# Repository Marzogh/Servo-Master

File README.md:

# Servo-Master
A family of servo controllers based on AVR µCs

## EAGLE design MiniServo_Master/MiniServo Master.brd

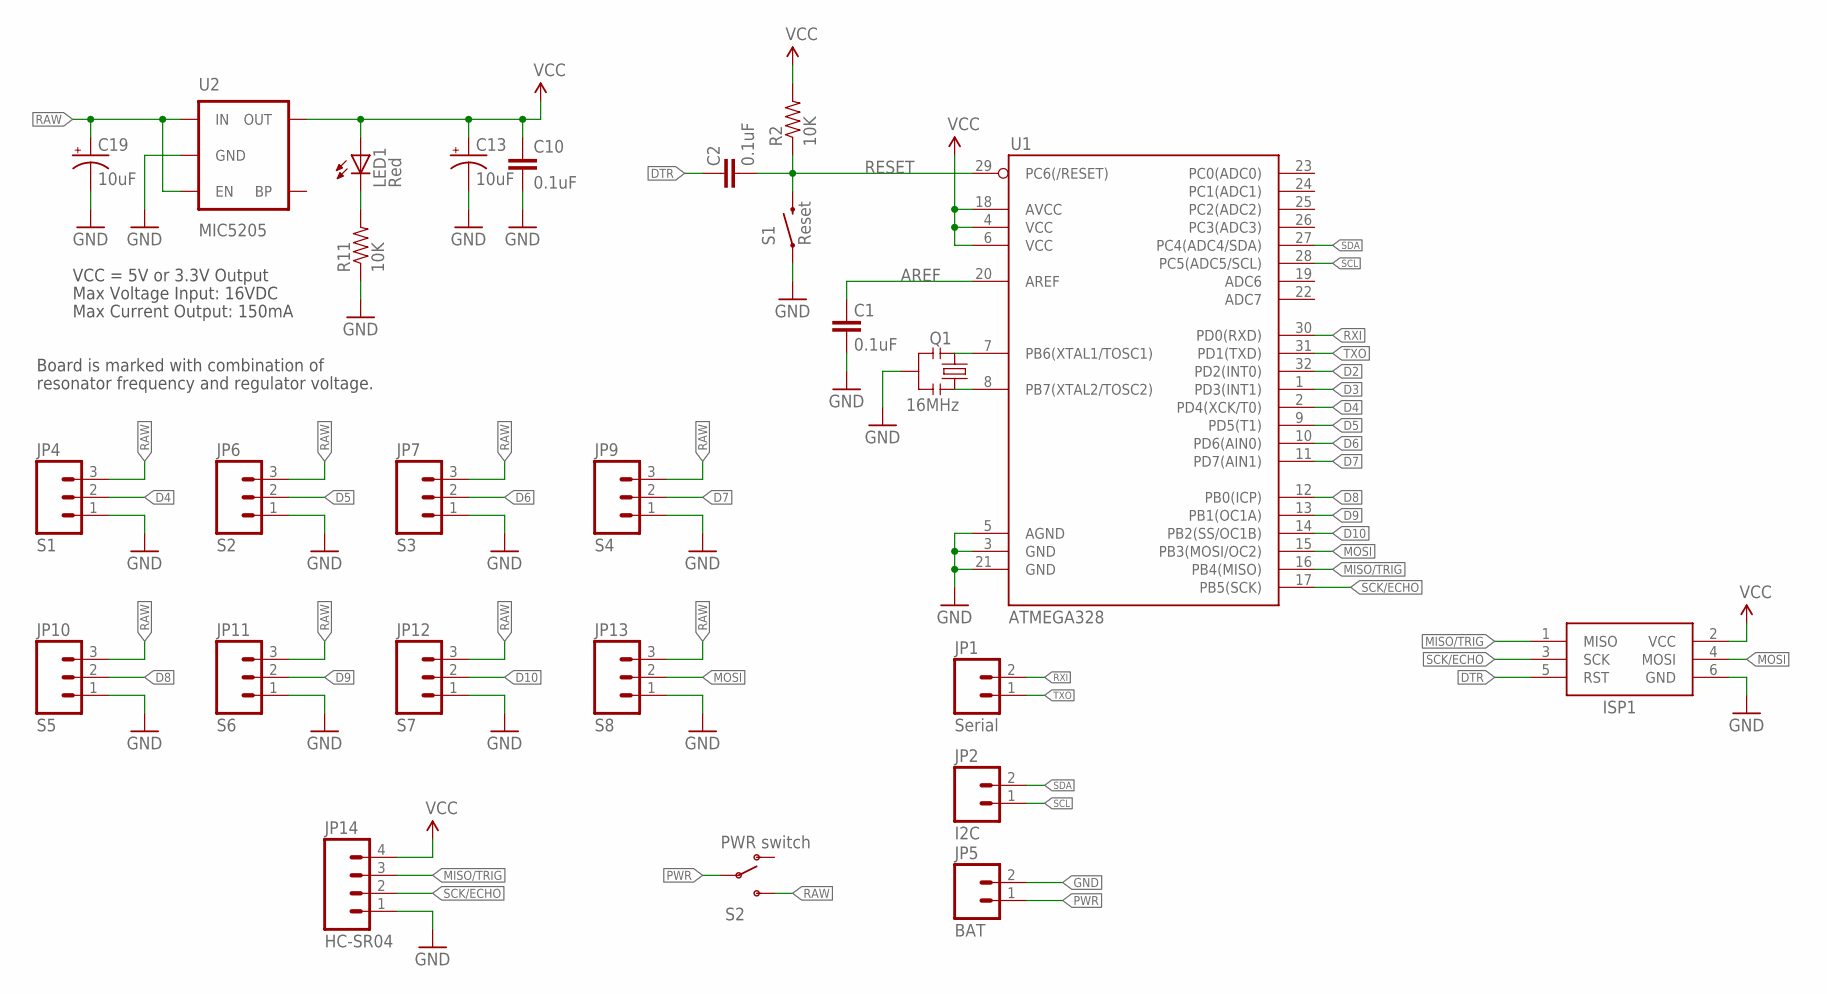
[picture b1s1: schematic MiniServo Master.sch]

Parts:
C1, C2, C10: 0.1uF; 0603-CAP
C13, C19: 10uF; EIA3216
ISP1: AVRISP-6; AVRISP
JP1: Serial; 1X02_NO_SILK
JP2: I2C; 1X02_NO_SILK
JP4: S1; 1X03_NO_SILK
JP5: BAT; 1X02_NO_SILK
JP6: S2; 1X03_NO_SILK
JP7: S3; 1X03_NO_SILK
JP9: S4; 1X03_NO_SILK
JP10: S5; 1X03_NO_SILK
JP11: S6; 1X03_NO_SILK
JP12: S7; 1X03_NO_SILK
JP13: S8; 1X03_NO_SILK
JP14: HC-SR04; 1X04_NO_SILK
LED1: Red; 0603-LED-ALT1
Q1: 16MHz; RESONATOR-SMD-1:1
R2, R11: 10K; 0603-RES
S1: Reset; TACTILE-SWITCH-SMD-ALT01
S2: PWR switch; SWITCH-SPST-SMD-A
U1: ATMEGA328; TQFP32-08
U2: MIC5205; SOT23-5

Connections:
3.3V: ISP1.2 (VCC), JP14.4
AREF: C1.2, U1.20 (AREF)
D2: U1.32 (PD2(INT0))
D3: U1.1 (PD3(INT1))
D4: JP4.2, U1.2 (PD4(XCK/T0))
D5: JP6.2, U1.9 (PD5(T1))
D6: JP7.2, U1.10 (PD6(AIN0))
D7: JP9.2, U1.11 (PD7(AIN1))
D8: JP10.2, U1.12 (PB0(ICP))
D9: JP11.2, U1.13 (PB1(OC1A))
D10: JP12.2, U1.14 (PB2(SS/OC1B))
DTR: C2.2, ISP1.5 (RST)
GND: C1.1, C10.2, C13.C (-), C19.C (-), ISP1.6 (GND), JP4.1, JP5.2, JP6.1, JP7.1, JP9.1, JP10.1, JP11.1, JP12.1, JP13.1, JP14.1, Q1.2, R11.1, S1.1, S1.2 (1), U1.3 (GND), U1.5 (AGND), U1.21 (GND), U2.2 (GND)
MISO/TRIG: ISP1.1 (MISO), JP14.3, U1.16 (PB4(MISO))
MOSI: ISP1.4 (MOSI), JP13.2, U1.15 (PB3(MOSI/OC2))
unnamed: Q1.3, U1.8 (PB7(XTAL2/TOSC2))
unnamed: Q1.1, U1.7 (PB6(XTAL1/TOSC1))
unnamed: LED1.C, R11.2
PWR: JP5.1, S2.2
RAW: C19.A (+), JP4.3, JP6.3, JP7.3, JP9.3, JP10.3, JP11.3, JP12.3, JP13.3, S2.3 (S), U2.1 (IN), U2.3 (EN)
RESET: C2.1, R2.1, S1.3 (2), S1.4 (2), U1.29 (PC6(/RESET))
RXI: JP1.2, U1.30 (PD0(RXD))
SCK/ECHO: ISP1.3 (SCK), JP14.2, U1.17 (PB5(SCK))
SCL: JP2.1, U1.28 (PC5(ADC5/SCL))
SDA: JP2.2, U1.27 (PC4(ADC4/SDA))
TXO: JP1.1, U1.31 (PD1(TXD))
VCC: C10.1, C13.A (+), LED1.A, R2.2, U1.4 (VCC), U1.6 (VCC), U1.18 (AVCC), U2.5 (OUT)

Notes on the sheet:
Max Voltage Input: 16VDC
Max Current Output: 150mA
Board is marked with combination of
resonator frequency and regulator voltage.
VCC = 5V or 3.3V Output

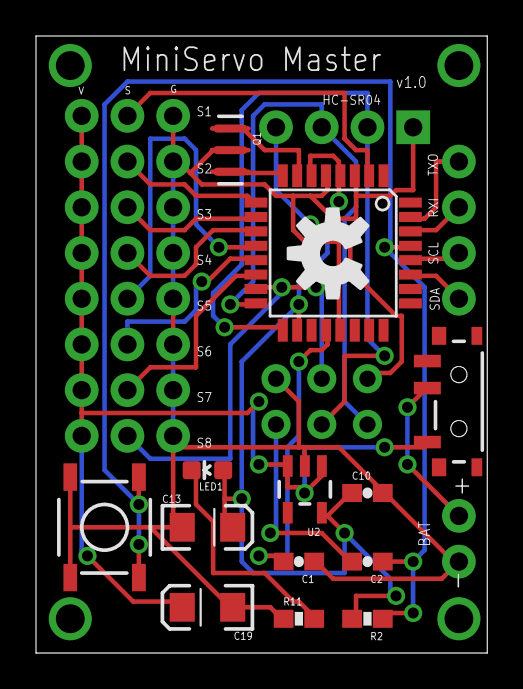
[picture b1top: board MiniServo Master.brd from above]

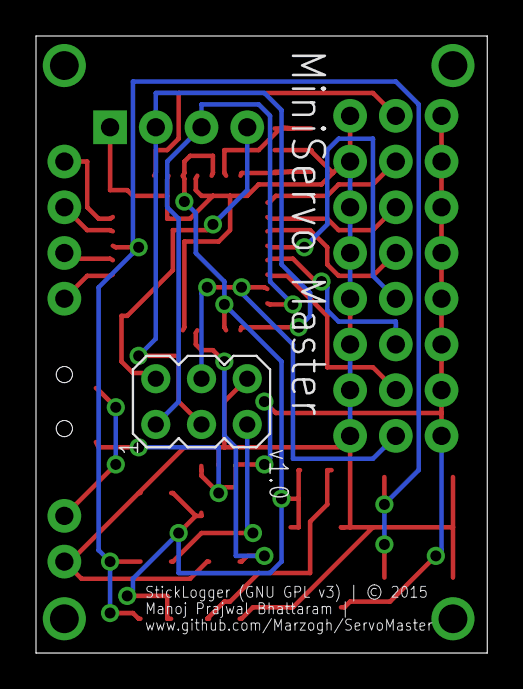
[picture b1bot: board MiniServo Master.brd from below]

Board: 2 copper layers, 25.1 x 34.3 mm, 27 parts (10 on the bottom side), 25 nets.

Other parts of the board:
U$1: OSHW-LOGO-M

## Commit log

2015-10-27 v1.0 board files + gerbers for SeeedStudio and OSHPark
2015-10-27 fixed board drills
2015-10-27 fixed board routing and vias
2015-10-27 fixed silkscreen
2015-10-27 changed directory tree

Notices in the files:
MiniServo_Master/MiniServo Master.brd:
StickLogger (GNU GPL v3) | © 2015
parts and their libraries:
SparkFun-Connectors: Licensing: Creative Commons ShareAlike 4.0 International - https://creativecommons.org/licenses/by-sa/4.0
